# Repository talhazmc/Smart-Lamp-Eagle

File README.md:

# Smart RGB Lamp with Bluetooth and Sound Control

This repository contains my smart lamp project developed using Arduino Nano, Bluetooth communication, RGB LED control, and a microphone sound sensor module.

The project was designed as an embedded systems application that allows an RGB lamp to be controlled wirelessly via Bluetooth and also react to sound input detected by a microphone module.

---

## Project Overview

The main purpose of this project was to build a smart lighting system by combining hardware and software components.

The system uses an Arduino Nano as the main controller. RGB LEDs are used as the lighting output, while a Bluetooth module enables wireless control. A microphone sensor module is used to detect sound levels and create sound-reactive lighting behavior.

---

## Features

* Bluetooth-based wireless control
* RGB LED color control
* Sound-reactive lighting using microphone sensor module
* Arduino Nano based embedded system
* Breadboard prototype and custom circuit board implementation
* Basic user-interactive smart lamp structure

---

## Working Principle

The Arduino Nano controls the RGB LED outputs according to the received input signals.

The Bluetooth module allows the lamp to receive wireless commands from a phone or another Bluetooth-enabled device. These commands can be used to change the lighting mode or RGB color behavior.

The microphone sensor module detects sound intensity from the environment. According to the detected sound level, the Arduino changes the RGB LED output, creating a sound-reactive lamp effect.

---

## Prototype

The first version of the project was tested on a breadboard with Arduino Nano, RGB LEDs, Bluetooth module, and microphone sensor module.

---

## Circuit Board

After testing the circuit, the components were assembled on a perforated prototype board to create a more stable hardware setup.

---

## Demo Video

A demo video of the smart lamp can be found here:

https://github.com/user-attachments/assets/2ac9d521-8023-4056-b593-29587c2fdeff

---

## Main Components

* Arduino Nano
* RGB LEDs / LED strip
* Bluetooth module
* Microphone sound sensor module
* Resistors
* Jumper wires
* Breadboard
* Perforated prototype board
* External lamp body / diffuser

---

## What I Learned

Through this project, I gained practical experience in:

* Arduino-based embedded system development
* RGB LED control
* Bluetooth communication
* Sound sensor integration
* Analog/digital sensor reading
* Breadboard prototyping
* Moving a prototype circuit to a perforated board
* Building an interactive lighting system

---

## Tools and Technologies

* Arduino Nano
* Arduino IDE
* C/C++
* Bluetooth communication
* Microphone sensor module
* RGB LED control
* Embedded systems prototyping

---

## Author

**Talha Üzümcü**
Electrical and Electronics Engineer
GitHub: [talhazmc](https://github.com/talhazmc)

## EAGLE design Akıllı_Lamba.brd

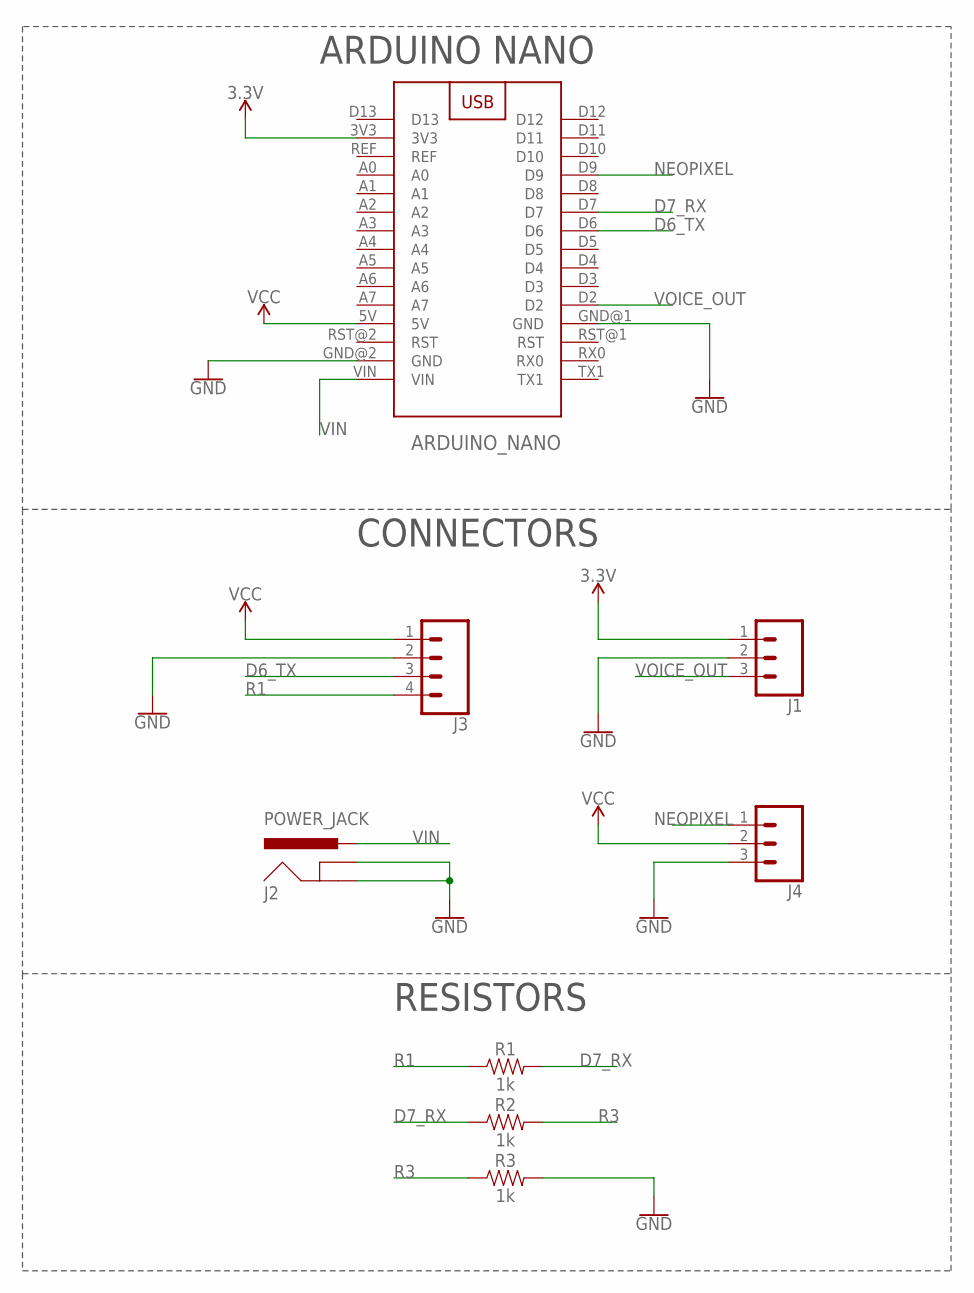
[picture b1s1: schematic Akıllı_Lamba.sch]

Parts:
ARDUINO_NANO: ARDUINONANO
J1, J4: 455-1750-1-ND; 1X03
J2: POWER_JACK; POWER_JACK_PTH
J3: CONN_04PTH; 1X04
R1, R2, R3: 1k; AXIAL-0.3

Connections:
3.3V: ARDUINO_NANO.3V3, J1.1
D6_TX: ARDUINO_NANO.D6, J3.3
D7_RX: ARDUINO_NANO.D7, R1.P$2 (2), R2.P$1 (1)
GND: ARDUINO_NANO.GND@1 (GND), ARDUINO_NANO.GND@2 (GND), J1.2, J2.GND, J2.GNDBREAK, J3.2, J4.3, R3.P$2 (2)
NEOPIXEL: ARDUINO_NANO.D9, J4.1
R1: J3.4, R1.P$1 (1)
R3: R2.P$2 (2), R3.P$1 (1)
VCC: ARDUINO_NANO.5V, J3.1, J4.2
VIN: ARDUINO_NANO.VIN, J2.PWR
VOICE_OUT: ARDUINO_NANO.D2, J1.3

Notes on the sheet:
ARDUINO NANO
CONNECTORS
RESISTORS

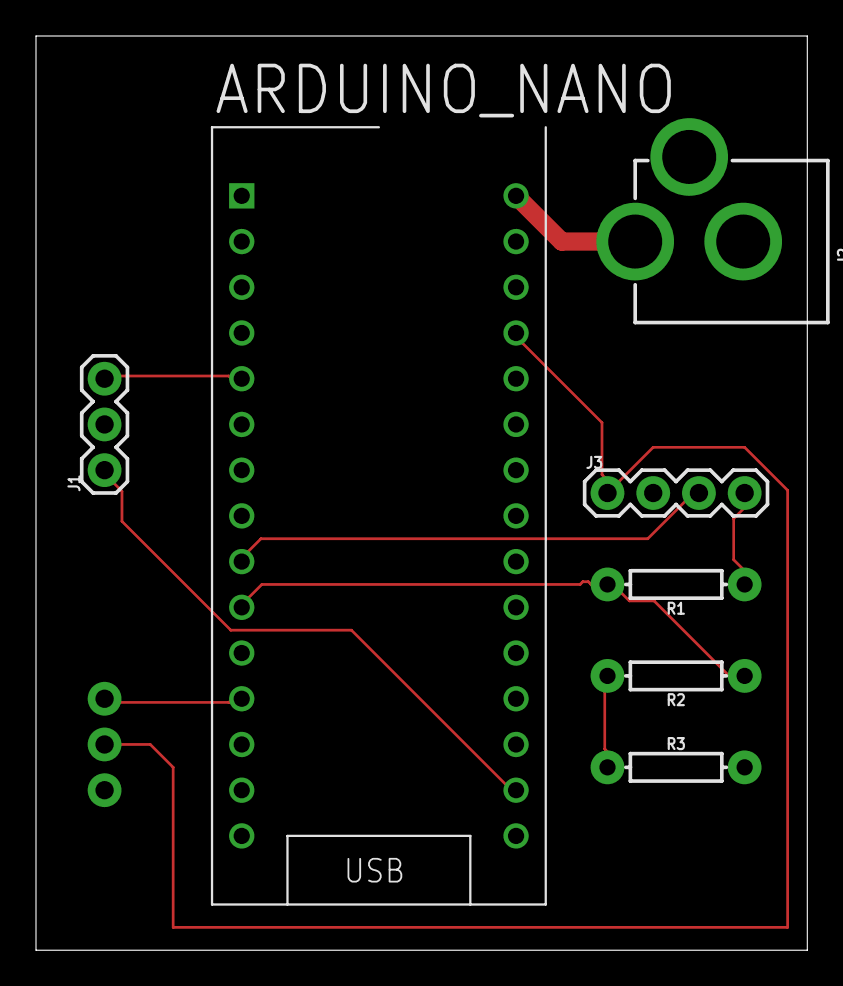
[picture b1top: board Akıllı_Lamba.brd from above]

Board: 2 copper layers, 42.9 x 50.8 mm, 8 parts (1 on the bottom side), 10 nets.

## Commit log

2026-06-24 Upload video and photos
2026-06-24 images file
2026-06-24 Add README for Smart RGB Lamp project
    This README provides an overview of the smart RGB lamp project, detailing its features, working principle, components, and lessons learned.
2026-06-24 Update demo video link from videos to images
2026-06-24 Add demo video link to README
    Added a link to the demo video of the smart lamp.
2026-06-24 Update demo video links in README.md
    Updated demo video links in README.

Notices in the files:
parts and their libraries:
SparkFun-Connectors: Licensing: Creative Commons ShareAlike 4.0 International - https://creativecommons.org/licenses/by-sa/4.0
